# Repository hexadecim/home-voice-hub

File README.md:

# HVH-1 Home Voice Hub

HVH-1 is a single-board computer for home automation. It runs Home Assistant OS and works as a Claude-powered voice assistant: the on-board microphone hears the request, Home Assistant turns it into text, Claude (the Anthropic conversation agent) decides what to do and answers, and Piper speaks the answer through the on-board speaker amplifier.

This repository has everything needed to make one: schematic, 6-layer PCB, fabrication files with JLCPCB BOM and placement, a 3D-printed enclosure, and an SD-card image that installs the latest Home Assistant OS configured for this hardware.

> **Status: design complete, not yet prototyped.** Every footprint is checked against its part's pinout, and the schematic netlist matches `design.py` (132 parts, 103 nets, 0 errors). The board is fully routed and passes KiCad 7 DRC with **0 errors and 0 unconnected pads**. The only 4 warnings are silkscreen on the USB-C jack and the mute switch, which overhang the board edge on purpose. Every assembled part was in stock at LCSC when this was generated, except the MGM210P (see below). No board has been built or powered yet, so read the risk register before ordering more than a prototype batch.

## Contents

| Folder | What is in it |
|---|---|
| `kicad/` | KiCad 7 project: `hvh.kicad_sch` (7 sheets), the routed and filled `hvh.kicad_pcb`, symbol library and project rules. Open `hvh.kicad_pro` |
| `lib/hvh.pretty/` | Custom footprints (CM5 DF40 connectors, CM5 outline, MGM210P, RJ45, USB3-A, MEMS mic) |
| `fab/` | Gerber/drill zip (6 copper layers), JLCPCB BOM + CPL (111 placements, 46 line items), full BOM with sourcing and stock, board STEP, schematic PDF, top/bottom assembly PDFs, netlist |
| `enclosure/` | Base and lid as STL, 3MF and STEP, plus an assembly STEP |
| `image/` | SD-card image builder, configuration example, GitHub Actions workflow, Claude/voice provisioning script |
| `image/out/` | Pre-built `hvh1-haos-18.5.img.xz` (Ethernet first boot, no credentials inside) |
| `gen/` | Python generators that produce all of the above from `design.py` (single source of truth) |

## Hardware summary

| Function | Implementation |
|---|---|
| Compute | Raspberry Pi **Compute Module 5** (BCM2712, 4x Cortex-A76 2.4 GHz). Designed for CM5 Lite Wireless (CM5104000, 4 GB), but works with any CM5 (eMMC variants boot from eMMC instead of the microSD) |
| Wi-Fi / Bluetooth | On the CM5: 802.11ac **2.4 + 5 GHz**, Bluetooth 5.0 / BLE. PCB antenna, or the U.FL connector through the enclosure SMA knock-out |
| Zigbee / Thread | Silicon Labs **MGM210P** (EFR32MG21, +20 dBm, chip antenna), the same module as the Home Assistant Yellow, so it runs the official Yellow EmberZNet / OpenThread RCP firmware. Connects to the CM5 through a CP2102N USB-UART with hardware flow control |
| Power | **USB-C** input, 5 V. The CC lines go to the CM5, which negotiates 5 V / 5 A with the Raspberry Pi 27 W supply. Power button (SW1) uses the CM5 on/off/shutdown logic |
| USB-A | 1x **USB 3.0** (CM5 native, 5 Gbit/s) + 1x **USB 2.0** (hub port). Each port has a TPS2553 switch (about 1.0 A) and TPD4EUSB30 ESD protection |
| USB 2.0 hub | Terminus FE1.1s, 4 ports: USB-A, audio codec, Zigbee bridge, and one spare port on test points TP12/TP13 |
| Microphone | ZTS6216 analog MEMS mic (top port, 65 dB SNR). Feeds a CM108B USB audio codec, which shows up as a standard USB sound card (snd-usb-audio). **Mute** slide switch SW4 cuts the mic supply in hardware and lights the red mute LED |
| Speaker | CM108B line out to a PAM8302A 2.5 W class-D amp, then JST-PH J6 for a 4-8 ohm speaker (36 mm driver in the lid) |
| Ethernet | Gigabit (CM5 PHY) to a HanRun HR911130A MagJack with LEDs |
| Storage | **microSD** (Molex 104031-0811) on the CM5 SD interface, with RT9742 power switching for UHS-I |
| Other | Fan header (J7, CM5 PWM + tach), RTC backup cell (J8), rpiboot button (SW2), Zigbee bootloader button (SW3), 4 status LEDs, debug UART and SWD test points |
| PCB | 100 x 80 mm, **6 layers** (JLC06161H-3313, 1.6 mm), controlled impedance: USB 90 ohm diff, Ethernet 100 ohm diff |

### Layer stack

| Layer | Use |
|---|---|
| L1 F.Cu | Components, high-speed signals, GND pour |
| L2 In1 | Solid GND (reference for L1) |
| L3 In2 | Low-speed signals and USB 2.0, GND pour |
| L4 In3 | +5 V plane |
| L5 In4 | Solid GND (reference for L6) |
| L6 B.Cu | Signals, test points, GND pour |

Routing: 1,650 track segments and 316 vias. Most traces are on L1, with L6 and L3 used for crossings.

Design rules:
- 0.15 mm clearance; standard vias 0.6 / 0.3 mm.
- Three filled vias are inside pads: the GND pins of U5 (0.45 / 0.2 mm) and U8 (0.35 / 0.15 mm). JLC fills and caps vias on 6-layer boards (POFV) at no extra cost; check that it is selected.

Trace geometry for the controlled-impedance pairs is 0.16 / 0.24 mm (USB, 90 ohm) and 0.14 / 0.26 mm (Ethernet, 100 ohm) on the outer layers. Order with **impedance control** and let JLC adjust the widths for their exact stack.

## Ordering the board (JLCPCB)

1. Upload `fab/HVH-1_gerbers_drill.zip`. Choose 6 layers, 1.6 mm, stack-up **JLC06161H-3313**, impedance control on, ENIG recommended (fine-pitch DF40 pads).
2. Turn on PCB Assembly, top side (plus bottom if you want the test-point side populated; the bottom only has test points, so top-only is fine).
3. Upload `fab/HVH-1_BOM_JLCPCB.csv` and `fab/HVH-1_CPL_JLCPCB.csv`. Check the rotation preview, especially SOT-23, QFN and the USB/RJ45 connectors.
4. **MGM210PA32JIA2:** LCSC stock is low. Use JLC Global Sourcing, or consign the part from DigiKey (336-MGM210PA32JIA2-ND).
5. The **CM5 module is not soldered**: plug it into J10/J11 and fit four M2.5 screws with 1.5 mm spacers.
6. **Factory step:** program a Gecko bootloader and the Yellow EmberZNet firmware into the MGM210P through the SWD test points (TP7 SWCLK, TP8 SWDIO, TP9 RESET, TP10 SWO, TP11 3V3A, GND). After that, firmware updates go over USB from Home Assistant.

`fab/HVH-1_BOM_full.csv` lists the manufacturer, MPN, LCSC number, stock snapshot, price and alternate source for every line.

## Enclosure

Print `enclosure/hvh1_base.3mf` and `enclosure/hvh1_lid.3mf`. The lid is already flipped top-down for printing. Use PETG or ASA (the CM5 runs warm), 0.2 mm layers, 3 walls, no supports.

**Hardware needed**
- 4x M3 x 10 socket-head screws and 4x M3 heat-set inserts in the lid pillars. These clamp the PCB between the base and the lid.
- 4x M2.5 heat-set inserts in the base, plus 4x M2.5 x 8 screws and 1.5 mm spacers for the CM5.
- A 36 mm, 8 ohm, 1-2 W speaker (5 mm deep), pressed into the lid ring and wired to J6.
- 4x 2 mm acrylic rods, 18 mm long, as LED light pipes.
- A 0.8 mm foam ring gasket between the mic tube and the PCB, and an acoustic mesh sticker on the outside of the mic hole.
- 4x 10 mm rubber feet.

**Openings**
- Rear: USB-C, USB-A x2, RJ45.
- Front: microSD (with finger notch) and the mute slide (the wall is thinned around the lever).
- Top: power key (cantilever with plunger), 4 LED pipes, mic port, speaker grille, CM5 vents, and pinholes for rpiboot and the Zigbee bootloader.
- Sides: vents, kept away from the Zigbee antenna wall.
- Right wall: SMA knock-out for an external Wi-Fi antenna.

There is about 13 mm of space above the CM5 for a heatsink. The Raspberry Pi CM5 passive heatsink fits; a fan can use J7.

## Software: SD-card image

`image/build_hvh_image.py` downloads the newest Home Assistant OS for the Raspberry Pi 5 / CM5 (`rpi5-64`), checks it, and writes the HVH-1 settings into the boot partition:

- **config.txt**, in a `[cm5]` section that is kept across HAOS updates:
  - full USB current
  - fan curve for J7
  - optional serial console on TP1/TP2
  - optional external antenna
  - optional RTC cell charging
- **cmdline.txt**: Wi-Fi regulatory country (needed for 5 GHz), and the serial console when enabled.
- **CONFIG/**, which HAOS imports at boot:
  - optional Wi-Fi keyfile
  - udev rule that names the Zigbee radio `/dev/ttyHVHZigbee`
  - optional SSH key

```
cd image
cp hvh-image.conf.example hvh-image.conf      # edit Wi-Fi, country, options
python3 build_hvh_image.py -c hvh-image.conf   # needs: xz, mtools  (macOS: brew install xz mtools)
```

The output is `hvh1-haos-<version>.img.xz`. Flash it with Raspberry Pi Imager ("Use custom") or balenaEtcher. It is a raw disk image (`.img`), the format SD cards and the CM5 boot ROM use; an `.iso` is only for optical media and PC installers.

The GitHub workflow `image/build-image.workflow.yml` (copy it to `.github/workflows/` in your repository) rebuilds the image every week against the newest HAOS release. Wi-Fi credentials come from repository secrets, so keep that repository private, because the built image contains them. A running device also updates itself through the normal HAOS updater.

## Setting up the Claude voice assistant

1. Boot the device (Ethernet, or the Wi-Fi from your config). Open `http://homeassistant.local:8123` and finish onboarding.
2. Create a long-lived access token: Profile > Security.
3. Get an API key from the Anthropic Console (console.anthropic.com).
4. Run the provisioning script from any computer on the network:

```
pip install websockets
python3 image/provision/hvh_provision.py --url http://homeassistant.local:8123 \
    --token <token> --anthropic-key <key> --hostname hvh1 --update-os
```

The `--update-os` run installs the newest HAOS and reboots the device. Run the script again without that flag. It then:

1. Installs and starts **Whisper** (speech to text) and **Piper** (text to speech).
2. Installs the **Assist Satellite** app (OHF-Voice/apps), which listens to the on-board mic for the wake word "Okay Nabu".
3. Makes the CM108B codec the default microphone and speaker.
4. Accepts the Wyoming and ESPHome discoveries.
5. Adds the **Anthropic** integration.
6. Creates the "HVH-1 Claude" Assist pipeline (Whisper > Claude > Piper) and sets it as preferred.

Claude can then answer questions and control the devices you expose to Assist. Check Settings > Voice assistants > Expose before giving it locks or alarms. Zigbee: Home Assistant offers to set up ZHA (or Thread/Matter) on the discovered radio; pick the "HVH-1 Zigbee" serial port.

## Risk register (read before production)

| # | Risk | Mitigation |
|---|---|---|
| 1 | No prototype built yet; the layout comes from a custom grid autorouter (`gen/router.py`), not hand routing | Order 5 boards first. Do bring-up in this order: power, CM5 boot, USB, Ethernet, audio, Zigbee. Get an independent EE review of the schematic PDF and layout |
| 2 | Impedance of the USB3 / Ethernet pairs depends on the fab stack-up | Order with impedance control and give the fab the target values (90 / 100 ohm diff) |
| 3 | HR911130A LED pin polarity taken from the EasyEDA model | Check LED orientation on the first boards; swapping only changes LED colour/behaviour |
| 4 | PCM12 slide switch, TS-1187A and other footprints come from the KiCad standard library | Check the JLC 3D preview / DFM before assembly |
| 5 | MGM210P has low LCSC stock and ships blank | Consign it from DigiKey; program the bootloader and firmware over SWD at the factory |
| 6 | Generic USB-C supplies give 5 V / 3 A, which limits USB port current | Use the Raspberry Pi 27 W USB-C supply (5 V / 5 A). `usb_max_current_enable=1` is set |
| 7 | Speaker and mic are in the same lid, so echo can cause false wake-ups | Gasket the mic tube; tune mic gain and noise suppression in the Assist Satellite options |
| 8 | Enclosure fit tolerances depend on the printer | Print the lid first and check the connector openings against the assembled board |
| 9 | `hvh_provision.py` uses Home Assistant APIs that change between releases; it has not been run against a live system | Every step can be skipped; the README steps can be done by hand in the UI |
| 10 | The CONFIG/network keyfile replaces all network connections at every boot |
| 11 | ESD channel choices: on U5 (USB3 ESD) the unused flow-through pads 7/9 are tied to GND. On U14 (Ethernet ESD), ETH2 uses pads 9/10. The TPD4EUSB30 pads 6/7/9/10 have no internal connection | Confirm against the TI datasheet during the EE review |
| 12 | 34 reference labels are hidden on the top silkscreen to avoid overlaps | Use the assembly PDFs, which show every reference, for bring-up and rework | Delete `CONFIG/network` from the boot partition after the first boot if you manage Wi-Fi in the UI |

## Rebuilding from source

All generators are in `gen/`. KiCad 7 Python (`pcbnew`), numba, shapely and CadQuery are needed.

```
python3 footprints.py && python3 schematic.py && python3 verify_sch.py   # library, schematic, netlist check
python3 pcb_place.py                                                      # board, placement, rules, planes
python3 router.py ../kicad/hvh.kicad_pcb routed.kicad_pcb                # grid router, 3 signal layers (about 1 h)
python3 repair.py routed.kicad_pcb repaired.kicad_pcb 25                  # rip-up/re-route hill climb on what is left
python3 postfix.py repaired.kicad_pcb fixed.kicad_pcb fix                 # GND via-in-pad, +5V stitching
python3 pcb_finish.py fixed.kicad_pcb ../kicad/hvh.kicad_pcb              # planes/pours, silkscreen, zone fill
python3 drc.py ../kicad/hvh.kicad_pcb drc.txt && python3 silkfix.py ../kicad/hvh.kicad_pcb drc.txt
python3 fab.py <pcb> ../kicad/hvh.kicad_sch ../fab                        # manufacturing outputs
python3 enclosure.py ../enclosure                                         # STL / 3MF / STEP
```

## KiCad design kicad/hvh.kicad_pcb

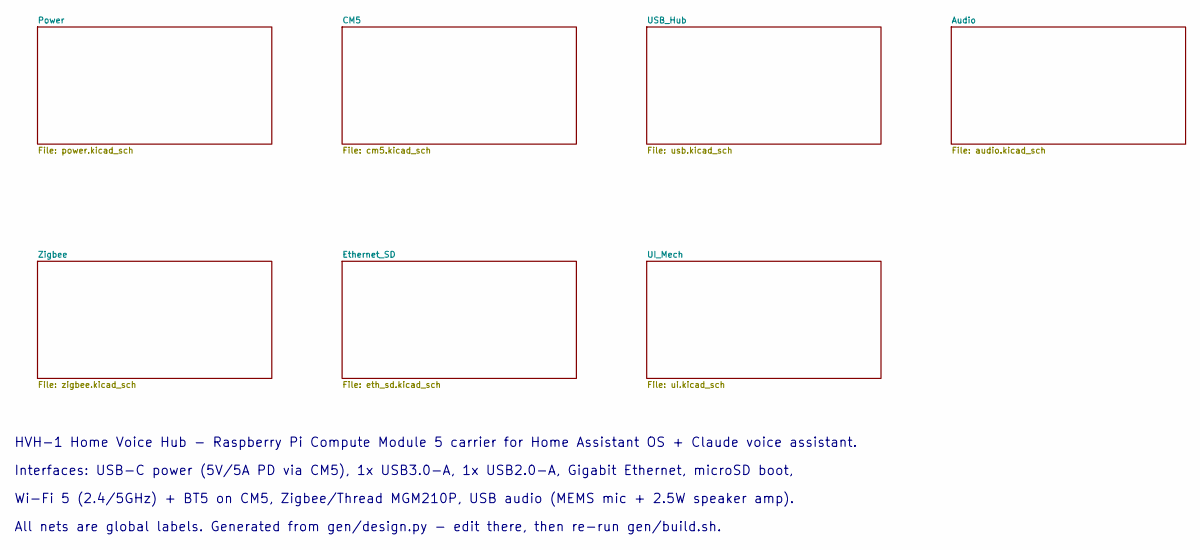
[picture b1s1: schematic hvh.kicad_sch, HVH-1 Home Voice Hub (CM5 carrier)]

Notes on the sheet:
HVH-1 Home Voice Hub - Raspberry Pi Compute Module 5 carrier for Home Assistant OS + Claude voice assistant.
Interfaces: USB-C power (5V/5A PD via CM5), 1x USB3.0-A, 1x USB2.0-A, Gigabit Ethernet, microSD boot,
Wi-Fi 5 (2.4/5GHz) + BT5 on CM5, Zigbee/Thread MGM210P, USB audio (MEMS mic + 2.5W speaker amp).
All nets are global labels. Generated from gen/design.py - edit there, then re-run gen/build.sh.

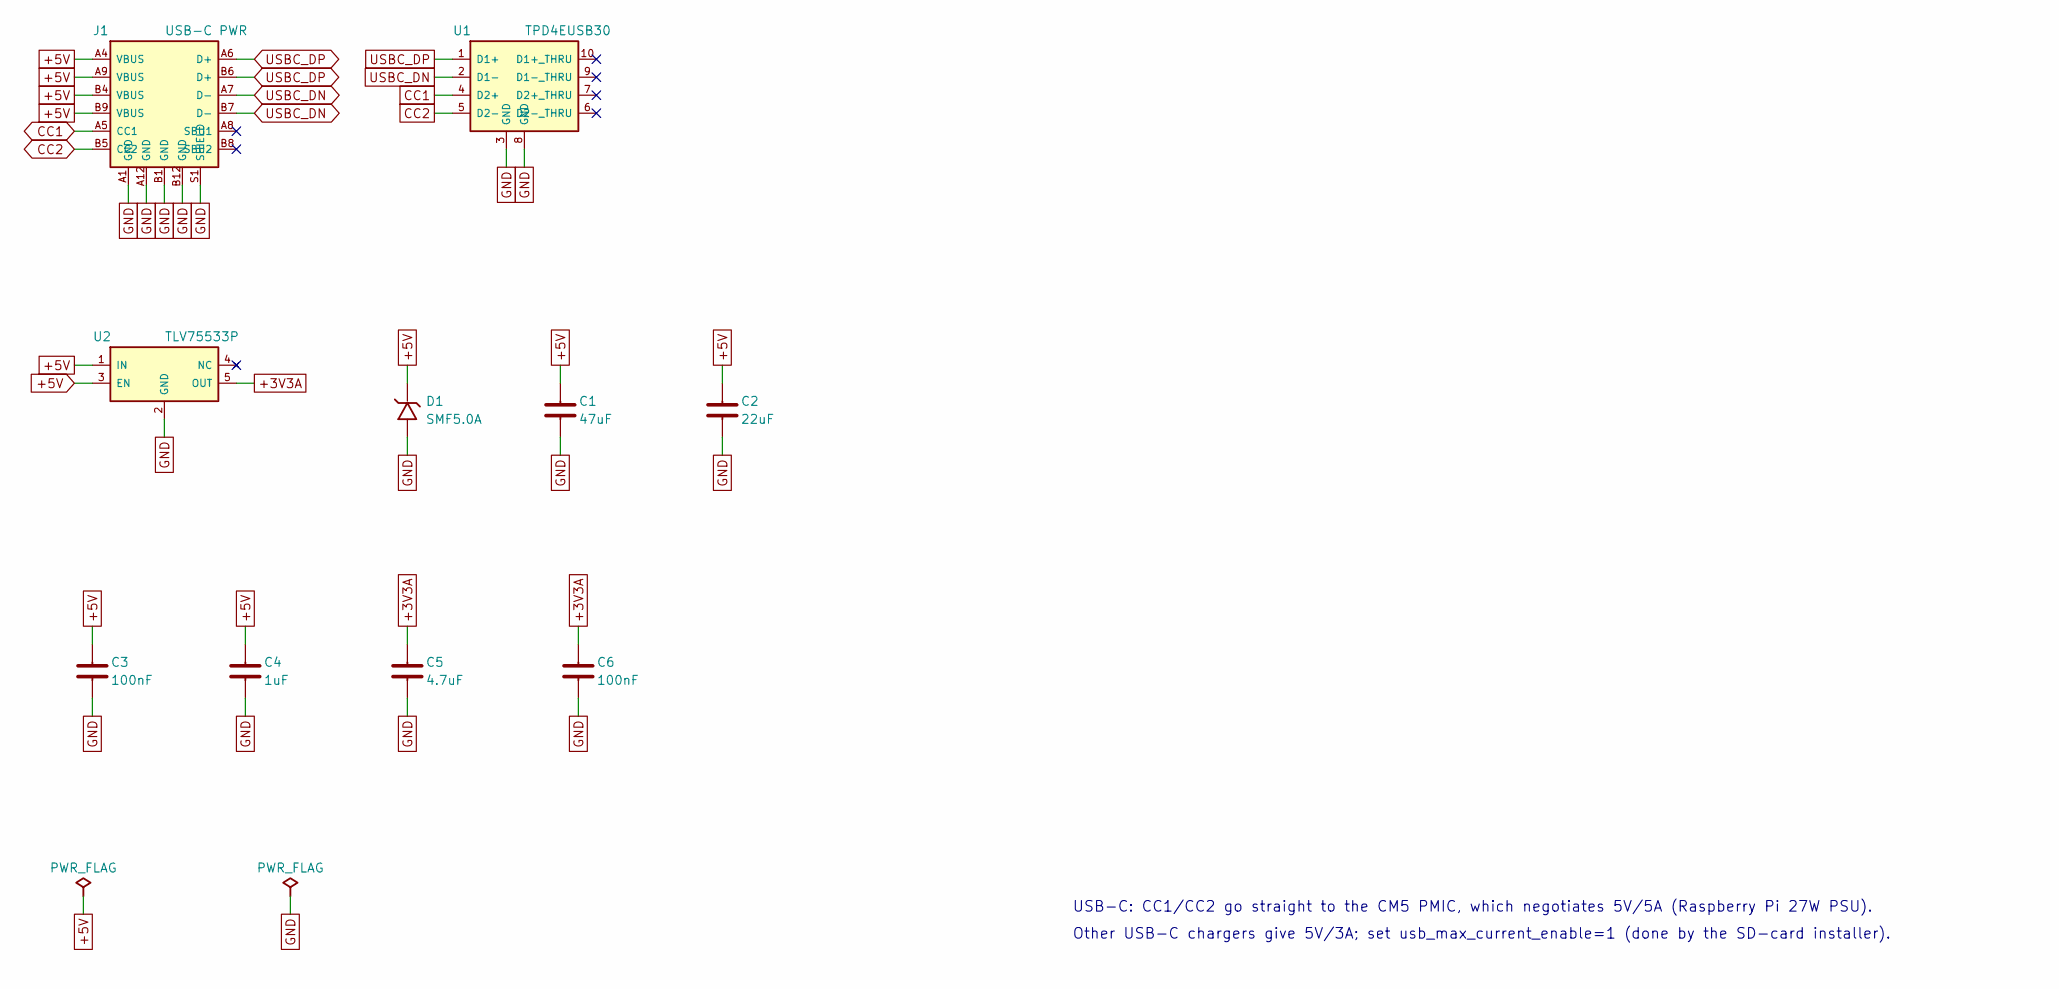
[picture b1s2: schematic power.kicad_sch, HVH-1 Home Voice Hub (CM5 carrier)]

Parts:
C1: 47uF; C_1206_3216Metric; MPN CL31A476MQHNNNE; LCSC C68361
C2: 22uF; C_0805_2012Metric; MPN CL21A226MAQNNNE; LCSC C45783
C3, C6: 100nF; C_0402_1005Metric; MPN CL05B104KO5NNNC; LCSC C1525
C4: 1uF; C_0402_1005Metric; MPN CL05A105KA5NQNC; LCSC C52923
C5: 4.7uF; C_0603_1608Metric; MPN CL10A475KO8NNNC; LCSC C19666
D1: SMF5.0A; D_SMF; MPN SMF5.0A; LCSC C193402
J1: USB-C PWR; USB_C_Receptacle_HRO_TYPE-C-31-M-12; MPN TYPE-C-31-M-12; LCSC C165948
U1: TPD4EUSB30; USON-10_2.5x1.0mm_P0.5mm; MPN TPD4EUSB30DQAR; LCSC C90627
U2: TLV75533P; SOT-23-5; MPN TLV75533PDBVR; LCSC C404027

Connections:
+3V3A: C5.1, C6.1, U2.5 (OUT); also elsewhere on the board
+5V: C1.1, C2.1, C3.1, C4.1, D1.1, J1.A4 (VBUS), J1.A9 (VBUS), J1.B4 (VBUS), J1.B9 (VBUS), U2.1 (IN), U2.3 (EN); also elsewhere on the board
CC1: J1.A5 (CC1), U1.4 (D2+); also elsewhere on the board
CC2: J1.B5 (CC2), U1.5 (D2-); also elsewhere on the board
GND: C1.2, C2.2, C3.2, C4.2, C5.2, C6.2, D1.2, J1.A1 (GND), J1.A12 (GND), J1.B1 (GND), J1.B12 (GND), J1.S1 (SHIELD), U1.3 (GND), U1.8 (GND), U2.2 (GND); also elsewhere on the board
USBC_DN: J1.A7 (D-), J1.B7 (D-), U1.2 (D1-); also elsewhere on the board
USBC_DP: J1.A6 (D+), J1.B6 (D+), U1.1 (D1+); also elsewhere on the board

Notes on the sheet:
USB-C: CC1/CC2 go straight to the CM5 PMIC, which negotiates 5V/5A (Raspberry Pi 27W PSU).
Other USB-C chargers give 5V/3A; set usb_max_current_enable=1 (done by the SD-card installer).

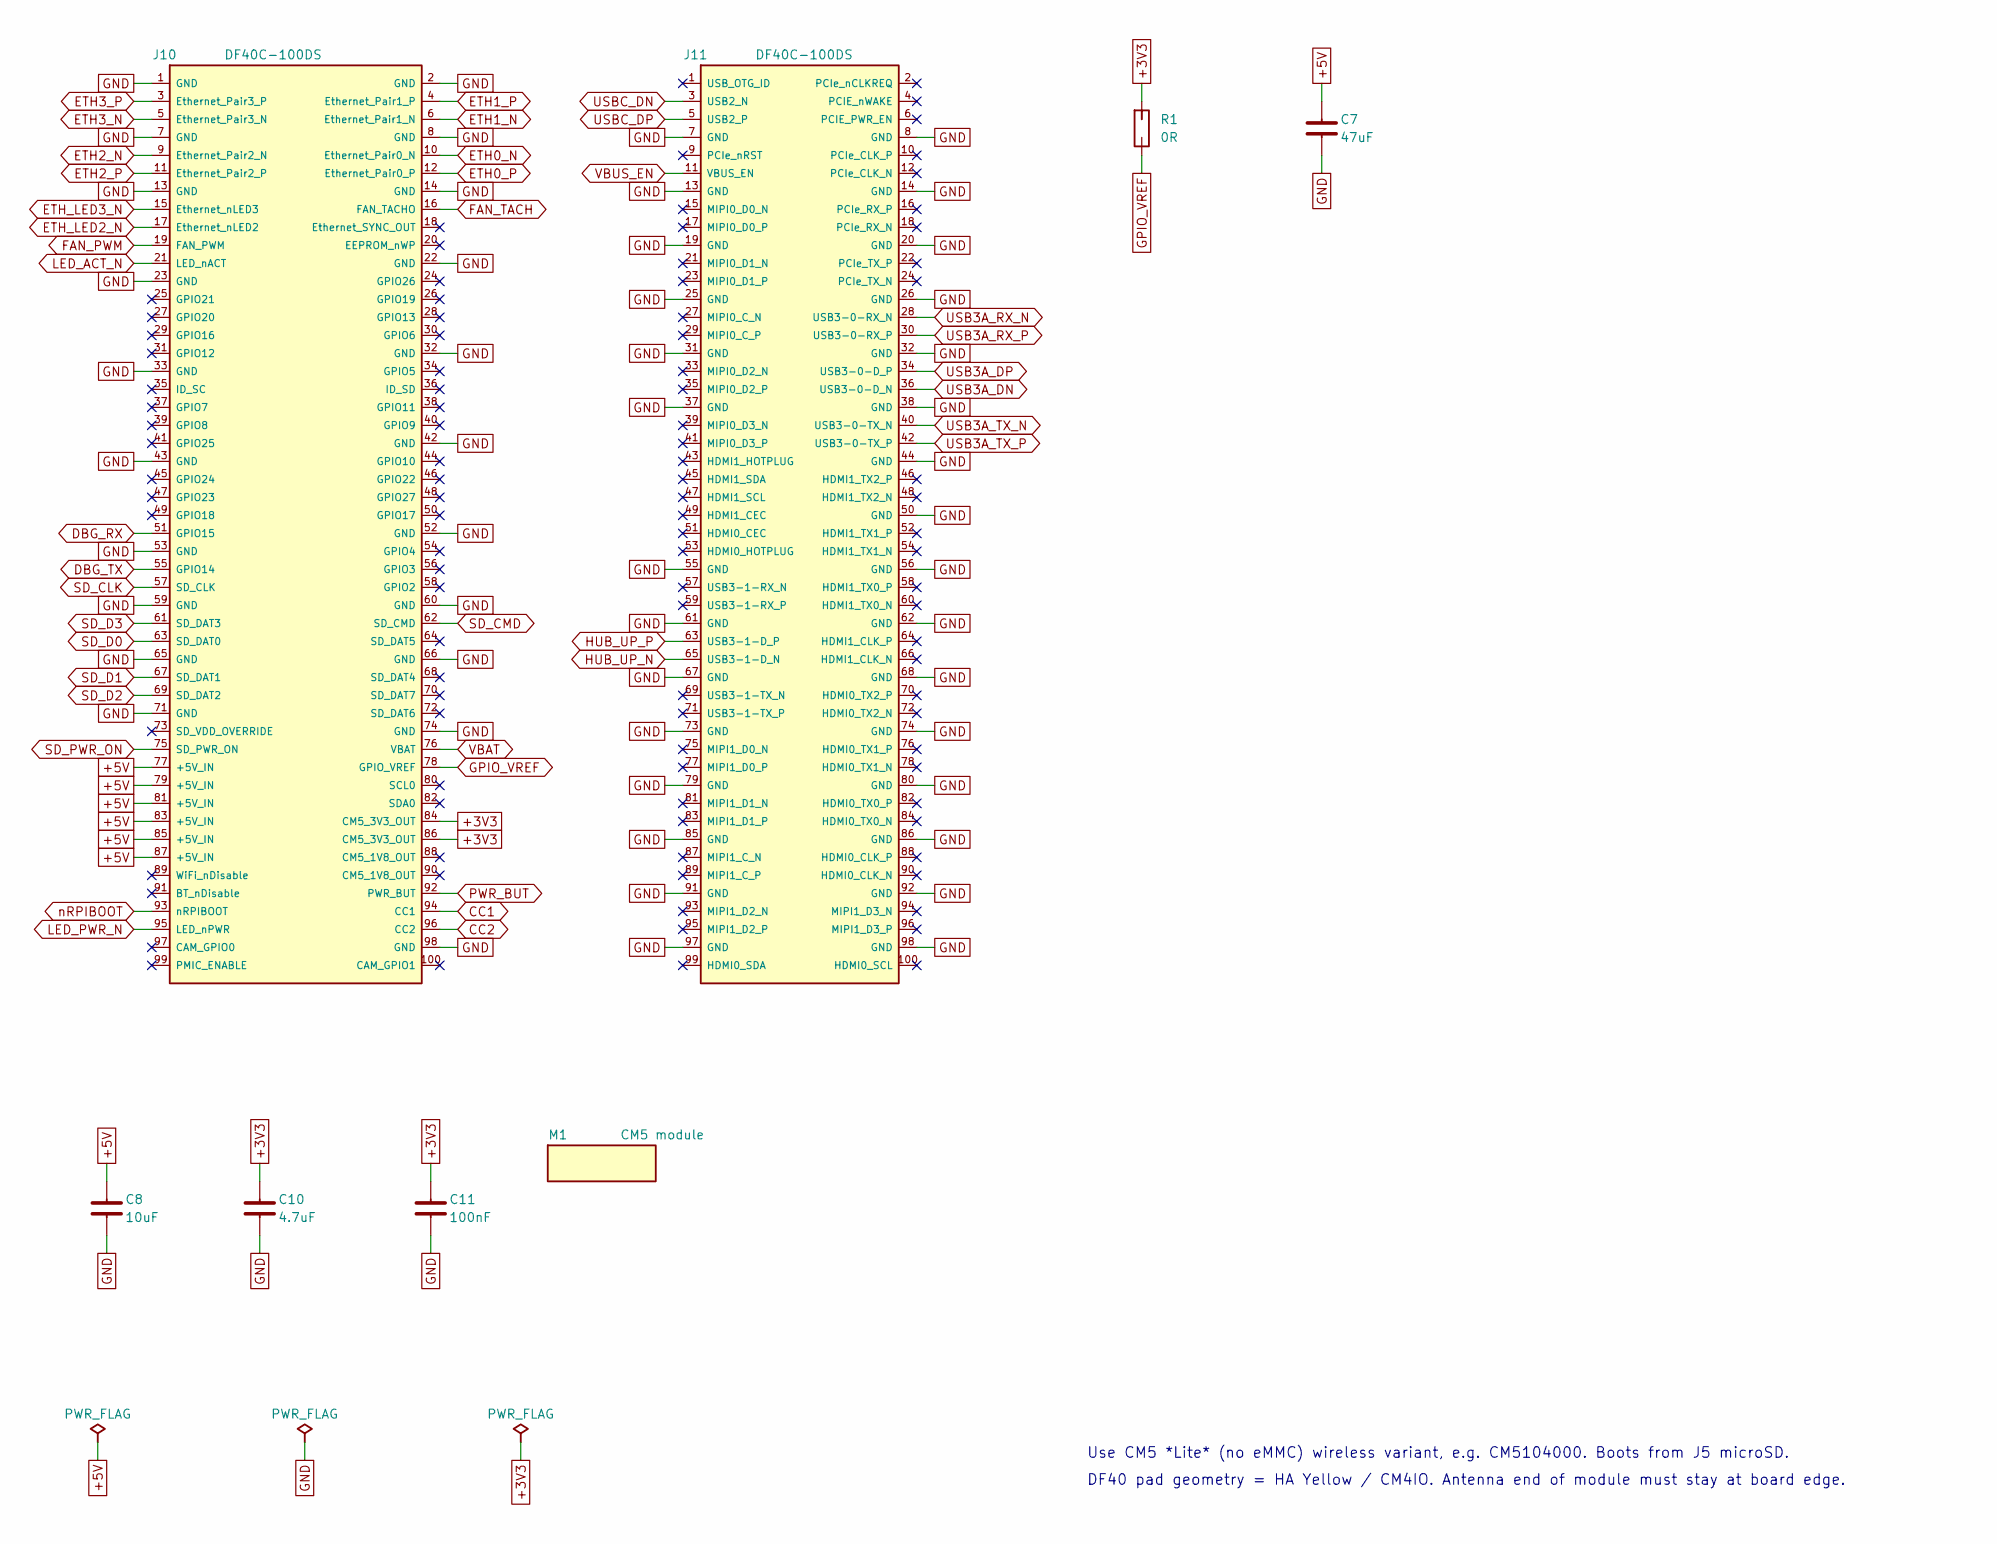
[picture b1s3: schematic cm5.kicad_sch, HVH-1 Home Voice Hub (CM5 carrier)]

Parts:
C7: 47uF; C_1206_3216Metric; MPN CL31A476MQHNNNE; LCSC C68361
C8: 10uF; C_0805_2012Metric; MPN CL21A106KAYNNNE; LCSC C15850
C10: 4.7uF; C_0603_1608Metric; MPN CL10A475KO8NNNC; LCSC C19666
C11: 100nF; C_0402_1005Metric; MPN CL05B104KO5NNNC; LCSC C1525
J10, J11: DF40C-100DS; CM5_DF40C-100DS-0.4V; MPN DF40C-100DS-0.4V(51); LCSC C597931
M1: CM5 module; CM5_Module_Mechanical; MPN CM5104000 (CM5 Lite, Wireless, 4GB)
R1: 0R; R_0402_1005Metric; MPN 0402WGF0000TCE; LCSC C17168

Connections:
+3V3: C10.1, C11.1, J10.84 (CM5_3V3_OUT), J10.86 (CM5_3V3_OUT), R1.1; also elsewhere on the board
+5V: C7.1, C8.1, J10.77 (+5V_IN), J10.79 (+5V_IN), J10.81 (+5V_IN), J10.83 (+5V_IN), J10.85 (+5V_IN), J10.87 (+5V_IN); also elsewhere on the board
CC1: J10.94 (CC1); also elsewhere on the board
CC2: J10.96 (CC2); also elsewhere on the board
DBG_RX: J10.51 (GPIO15); also elsewhere on the board
DBG_TX: J10.55 (GPIO14); also elsewhere on the board
ETH0_N: J10.10 (Ethernet_Pair0_N); also elsewhere on the board
ETH0_P: J10.12 (Ethernet_Pair0_P); also elsewhere on the board
ETH1_N: J10.6 (Ethernet_Pair1_N); also elsewhere on the board
ETH1_P: J10.4 (Ethernet_Pair1_P); also elsewhere on the board
ETH2_N: J10.9 (Ethernet_Pair2_N); also elsewhere on the board
ETH2_P: J10.11 (Ethernet_Pair2_P); also elsewhere on the board
ETH3_N: J10.5 (Ethernet_Pair3_N); also elsewhere on the board
ETH3_P: J10.3 (Ethernet_Pair3_P); also elsewhere on the board
ETH_LED2_N: J10.17 (Ethernet_nLED2); also elsewhere on the board
ETH_LED3_N: J10.15 (Ethernet_nLED3); also elsewhere on the board
FAN_PWM: J10.19 (FAN_PWM); also elsewhere on the board
FAN_TACH: J10.16 (FAN_TACHO); also elsewhere on the board
GND: C7.2, C8.2, C10.2, C11.2, J10.1 (GND), J10.2 (GND), J10.7 (GND), J10.8 (GND), J10.13 (GND), J10.14 (GND), J10.22 (GND), J10.23 (GND), J10.32 (GND), J10.33 (GND), J10.42 (GND), J10.43 (GND), J10.52 (GND), J10.53 (GND), J10.59 (GND), J10.60 (GND), J10.65 (GND), J10.66 (GND), J10.71 (GND), J10.74 (GND), J10.98 (GND), J11.7 (GND), J11.8 (GND), J11.13 (GND), J11.14 (GND), J11.19 (GND), J11.20 (GND), J11.25 (GND), J11.26 (GND), J11.31 (GND), J11.32 (GND), J11.37 (GND), J11.38 (GND), J11.44 (GND), J11.50 (GND), J11.55 (GND), J11.56 (GND), J11.61 (GND), J11.62 (GND), J11.67 (GND), J11.68 (GND), J11.73 (GND), J11.74 (GND), J11.79 (GND), J11.80 (GND), J11.85 (GND), J11.86 (GND), J11.91 (GND), J11.92 (GND), J11.97 (GND), J11.98 (GND); also elsewhere on the board
GPIO_VREF: J10.78 (GPIO_VREF), R1.2
HUB_UP_N: J11.65 (USB3-1-D_N); also elsewhere on the board
HUB_UP_P: J11.63 (USB3-1-D_P); also elsewhere on the board
LED_ACT_N: J10.21 (LED_nACT); also elsewhere on the board
LED_PWR_N: J10.95 (LED_nPWR); also elsewhere on the board
PWR_BUT: J10.92 (PWR_BUT); also elsewhere on the board
SD_CLK: J10.57 (SD_CLK); also elsewhere on the board
SD_CMD: J10.62 (SD_CMD); also elsewhere on the board
SD_D0: J10.63 (SD_DAT0); also elsewhere on the board
SD_D1: J10.67 (SD_DAT1); also elsewhere on the board
SD_D2: J10.69 (SD_DAT2); also elsewhere on the board
SD_D3: J10.61 (SD_DAT3); also elsewhere on the board
SD_PWR_ON: J10.75 (SD_PWR_ON); also elsewhere on the board
USB3A_DN: J11.36 (USB3-0-D_N); also elsewhere on the board
USB3A_DP: J11.34 (USB3-0-D_P); also elsewhere on the board
USB3A_RX_N: J11.28 (USB3-0-RX_N); also elsewhere on the board
USB3A_RX_P: J11.30 (USB3-0-RX_P); also elsewhere on the board
USB3A_TX_N: J11.40 (USB3-0-TX_N); also elsewhere on the board
USB3A_TX_P: J11.42 (USB3-0-TX_P); also elsewhere on the board
USBC_DN: J11.3 (USB2_N); also elsewhere on the board
USBC_DP: J11.5 (USB2_P); also elsewhere on the board
VBAT: J10.76 (VBAT); also elsewhere on the board
VBUS_EN: J11.11 (VBUS_EN); also elsewhere on the board
nRPIBOOT: J10.93 (nRPIBOOT); also elsewhere on the board

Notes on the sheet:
Use CM5 *Lite* (no eMMC) wireless variant, e.g. CM5104000. Boots from J5 microSD.
DF40 pad geometry = HA Yellow / CM4IO. Antenna end of module must stay at board edge.

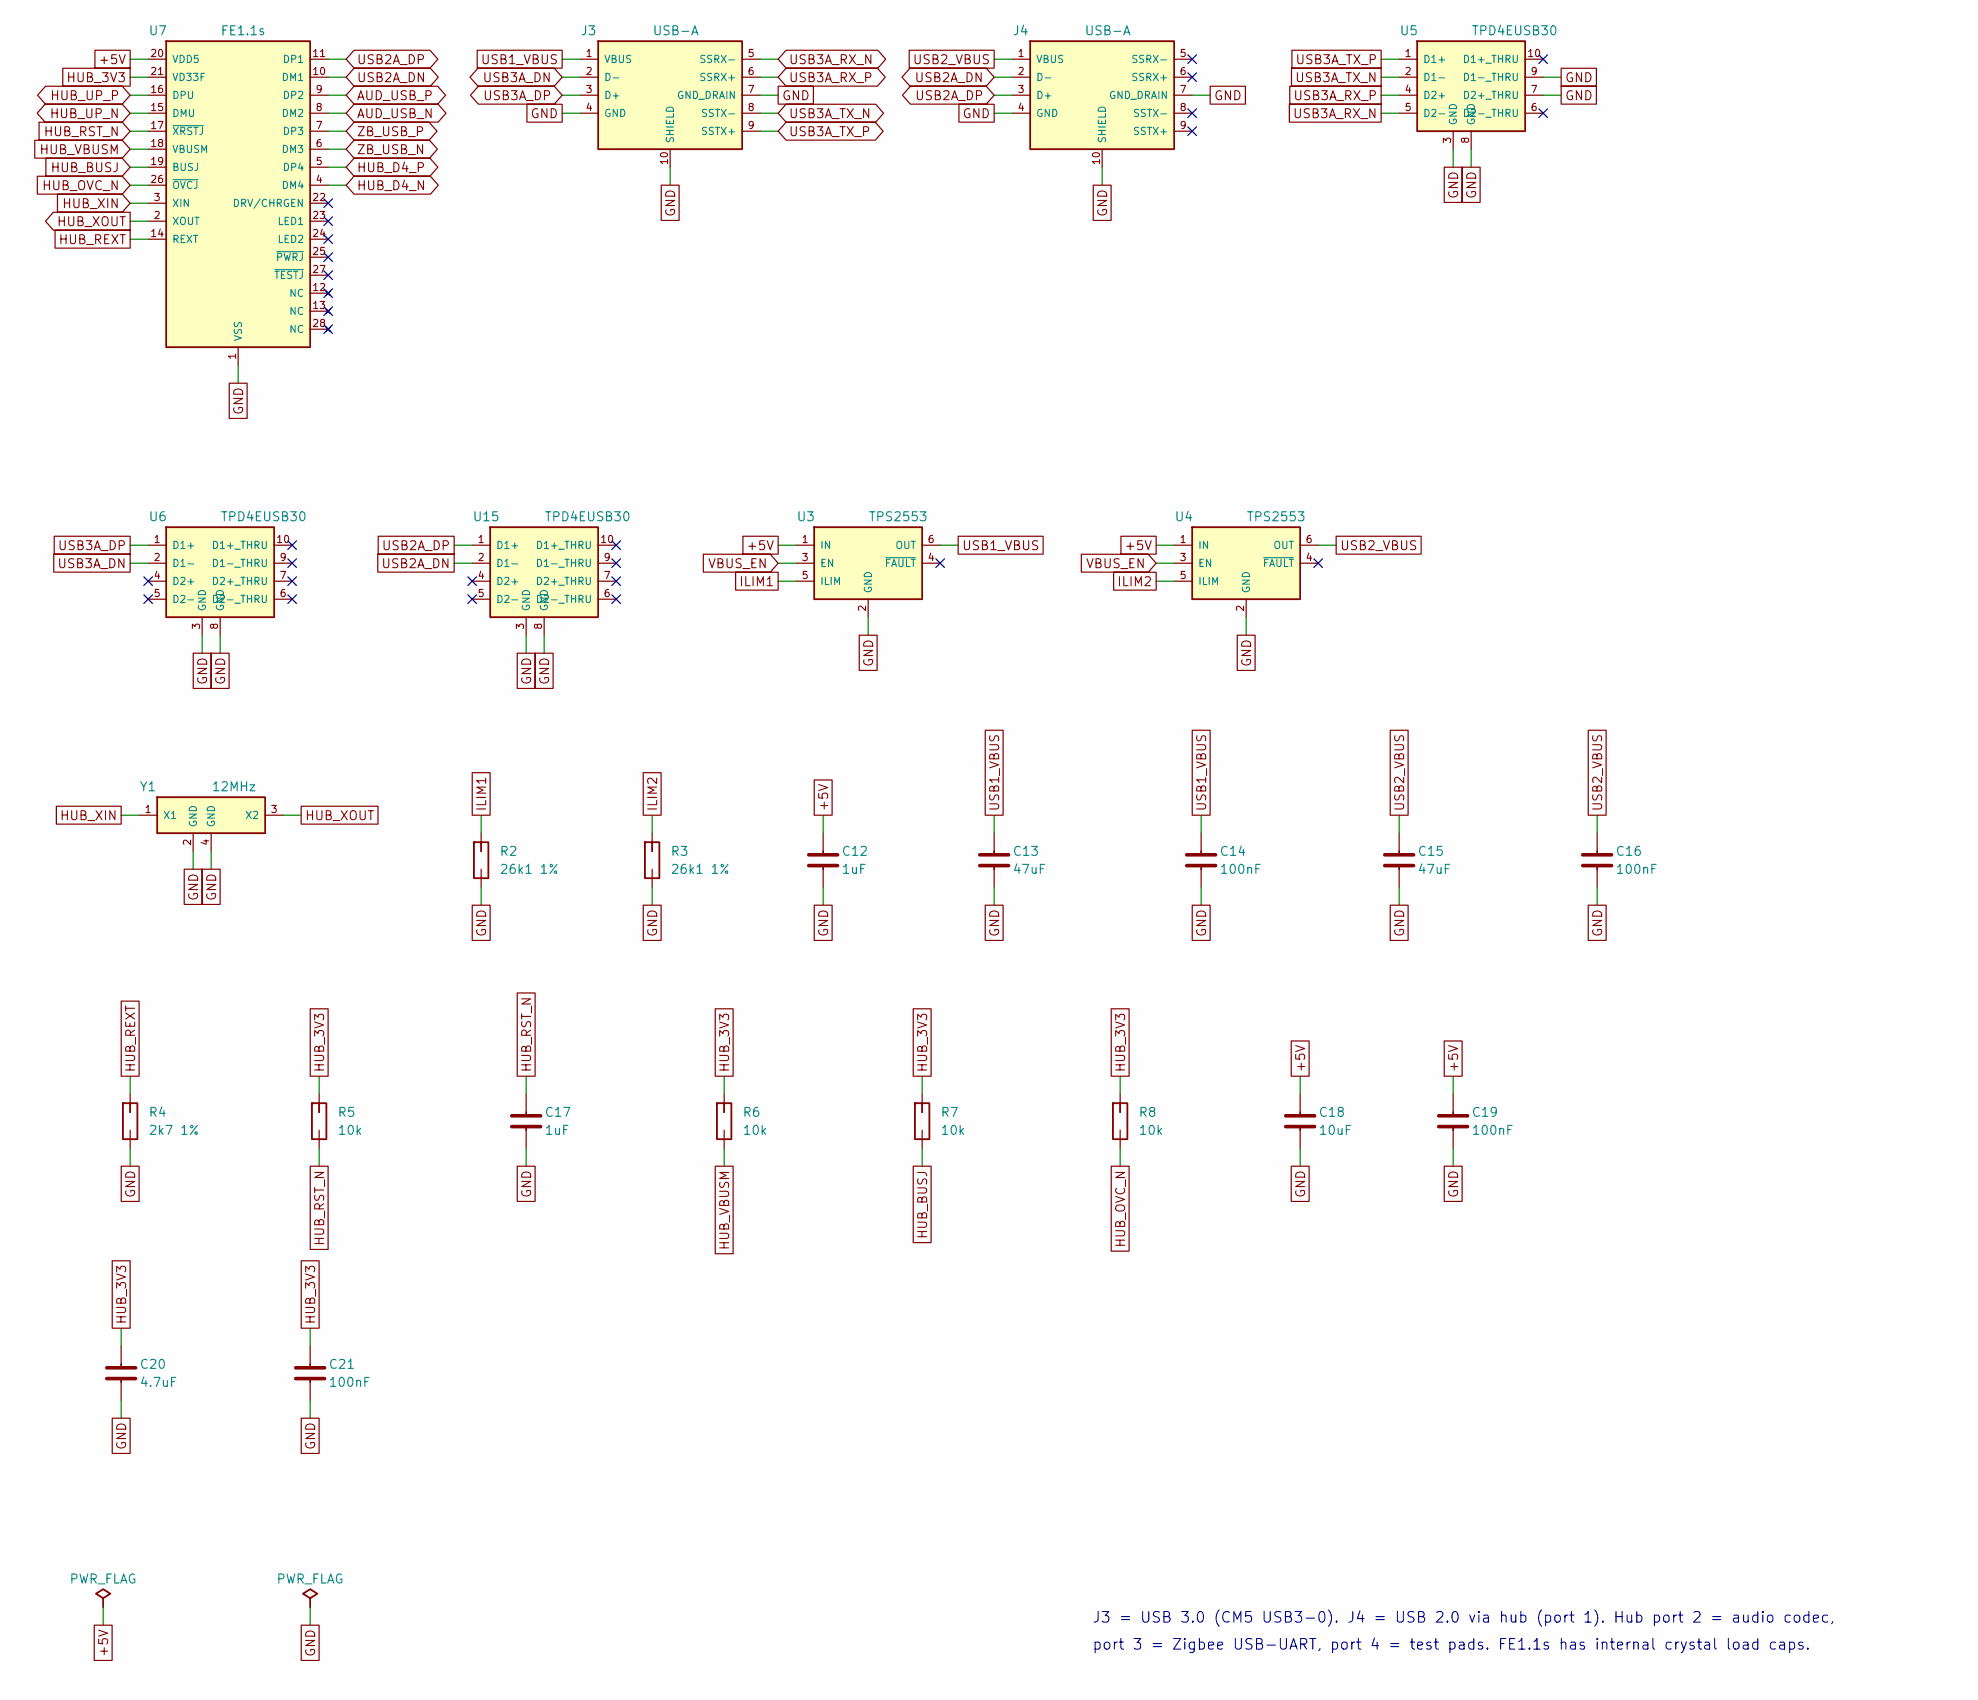
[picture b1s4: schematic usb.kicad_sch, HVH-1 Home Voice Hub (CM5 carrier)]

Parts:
C12, C17: 1uF; C_0402_1005Metric; MPN CL05A105KA5NQNC; LCSC C52923
C13, C15: 47uF; C_1206_3216Metric; MPN CL31A476MQHNNNE; LCSC C68361
C14, C16, C19, C21: 100nF; C_0402_1005Metric; MPN CL05B104KO5NNNC; LCSC C1525
C18: 10uF; C_0603_1608Metric; MPN CL10A106KP8NNNC; LCSC C19702
C20: 4.7uF; C_0603_1608Metric; MPN CL10A475KO8NNNC; LCSC C19666
J3, J4: USB-A; USB3_A_Amphenol_GSB311131HR; MPN GSB311131HR; LCSC C473057
R2, R3: 26k1 1%; R_0402_1005Metric; MPN RC0402FR-0726K1L; LCSC C155697
R4: 2k7 1%; R_0402_1005Metric; MPN 0402WGF2701TCE; LCSC C25885
R5, R6, R7, R8: 10k; R_0402_1005Metric; MPN 0402WGF1002TCE; LCSC C25744
U3, U4: TPS2553; SOT-23-6; MPN TPS2553DBVR; LCSC C55266
U5, U6, U15: TPD4EUSB30; USON-10_2.5x1.0mm_P0.5mm; MPN TPD4EUSB30DQAR; LCSC C90627
U7: FE1.1s; SSOP-28_3.9x9.9mm_P0.635mm; MPN FE1.1S-BSOP28BCN; LCSC C9359
Y1: 12MHz; Crystal_SMD_3225-4Pin_3.2x2.5mm; MPN X322512MSB4SI; LCSC C9002

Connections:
+5V: C12.1, C18.1, C19.1, U3.1 (IN), U4.1 (IN), U7.20 (VDD5); also elsewhere on the board
AUD_USB_N: U7.8 (DM2); also elsewhere on the board
AUD_USB_P: U7.9 (DP2); also elsewhere on the board
GND: C12.2, C13.2, C14.2, C15.2, C16.2, C17.2, C18.2, C19.2, C20.2, C21.2, J3.4 (GND), J3.7 (GND_DRAIN), J3.10 (SHIELD), J4.4 (GND), J4.7 (GND_DRAIN), J4.10 (SHIELD), R2.2, R3.2, R4.2, U3.2 (GND), U4.2 (GND), U5.3 (GND), U5.7 (D2+_THRU), U5.8 (GND), U5.9 (D1-_THRU), U6.3 (GND), U6.8 (GND), U7.1 (VSS), U15.3 (GND), U15.8 (GND), Y1.2 (GND), Y1.4 (GND); also elsewhere on the board
HUB_3V3: C20.1, C21.1, R5.1, R6.1, R7.1, R8.1, U7.21 (VD33F)
HUB_BUSJ: R7.2, U7.19 (BUSJ)
HUB_D4_N: U7.4 (DM4); also elsewhere on the board
HUB_D4_P: U7.5 (DP4); also elsewhere on the board
HUB_OVC_N: R8.2, U7.26 (~OVCJ)
HUB_REXT: R4.1, U7.14 (REXT)
HUB_RST_N: C17.1, R5.2, U7.17 (~XRSTJ)
HUB_UP_N: U7.15 (DMU); also elsewhere on the board
HUB_UP_P: U7.16 (DPU); also elsewhere on the board
HUB_VBUSM: R6.2, U7.18 (VBUSM)
HUB_XIN: U7.3 (XIN), Y1.1 (X1)
HUB_XOUT: U7.2 (XOUT), Y1.3 (X2)
ILIM1: R2.1, U3.5 (ILIM)
ILIM2: R3.1, U4.5 (ILIM)
USB1_VBUS: C13.1, C14.1, J3.1 (VBUS), U3.6 (OUT)
USB2A_DN: J4.2 (D-), U7.10 (DM1), U15.2 (D1-)
USB2A_DP: J4.3 (D+), U7.11 (DP1), U15.1 (D1+)
USB2_VBUS: C15.1, C16.1, J4.1 (VBUS), U4.6 (OUT)
USB3A_DN: J3.2 (D-), U6.2 (D1-); also elsewhere on the board
USB3A_DP: J3.3 (D+), U6.1 (D1+); also elsewhere on the board
USB3A_RX_N: J3.5 (SSRX-), U5.5 (D2-); also elsewhere on the board
USB3A_RX_P: J3.6 (SSRX+), U5.4 (D2+); also elsewhere on the board
USB3A_TX_N: J3.8 (SSTX-), U5.2 (D1-); also elsewhere on the board
USB3A_TX_P: J3.9 (SSTX+), U5.1 (D1+); also elsewhere on the board
VBUS_EN: U3.3 (EN), U4.3 (EN); also elsewhere on the board
ZB_USB_N: U7.6 (DM3); also elsewhere on the board
ZB_USB_P: U7.7 (DP3); also elsewhere on the board

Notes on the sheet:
J3 = USB 3.0 (CM5 USB3-0). J4 = USB 2.0 via hub (port 1). Hub port 2 = audio codec,
port 3 = Zigbee USB-UART, port 4 = test pads. FE1.1s has internal crystal load caps.
